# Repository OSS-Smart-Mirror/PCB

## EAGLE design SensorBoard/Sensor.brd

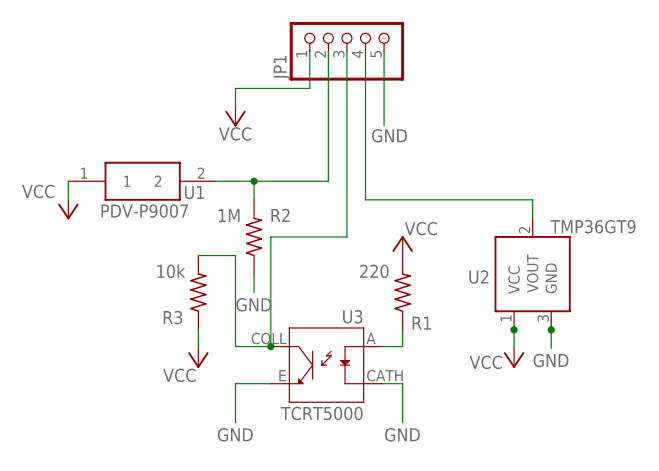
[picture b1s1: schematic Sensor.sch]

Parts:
JP1: PINHD-1X5; 1X05
R1: 220; R0805
R2: 1M; R0805
R3: 10k; R0805
U1: PDV-P9007
U2: TMP36GT9; TO-92
U3: TCRT5000; OPTO_TCRT5000

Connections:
GND: JP1.5, R2.1, U2.3 (GND), U3.CATH, U3.E
IR: JP1.3, R3.2, U3.COLL
LDR: JP1.2, R2.2, U1.2
unnamed: R1.1, U3.A
TEMP: JP1.4, U2.2 (VOUT)
VCC: JP1.1, R1.2, R3.1, U1.1, U2.1 (VCC)

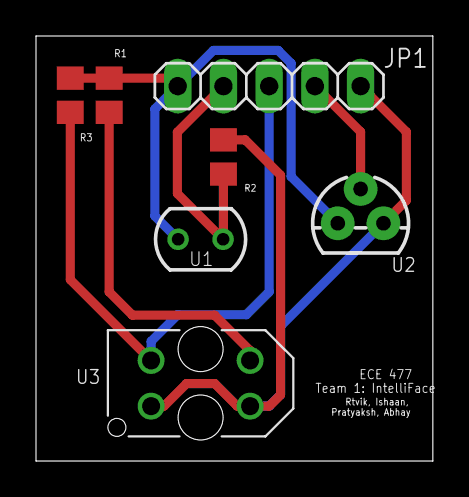
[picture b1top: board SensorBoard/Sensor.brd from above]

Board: 2 copper layers, 22.0 x 23.6 mm, 7 parts (0 on the bottom side), 6 nets.

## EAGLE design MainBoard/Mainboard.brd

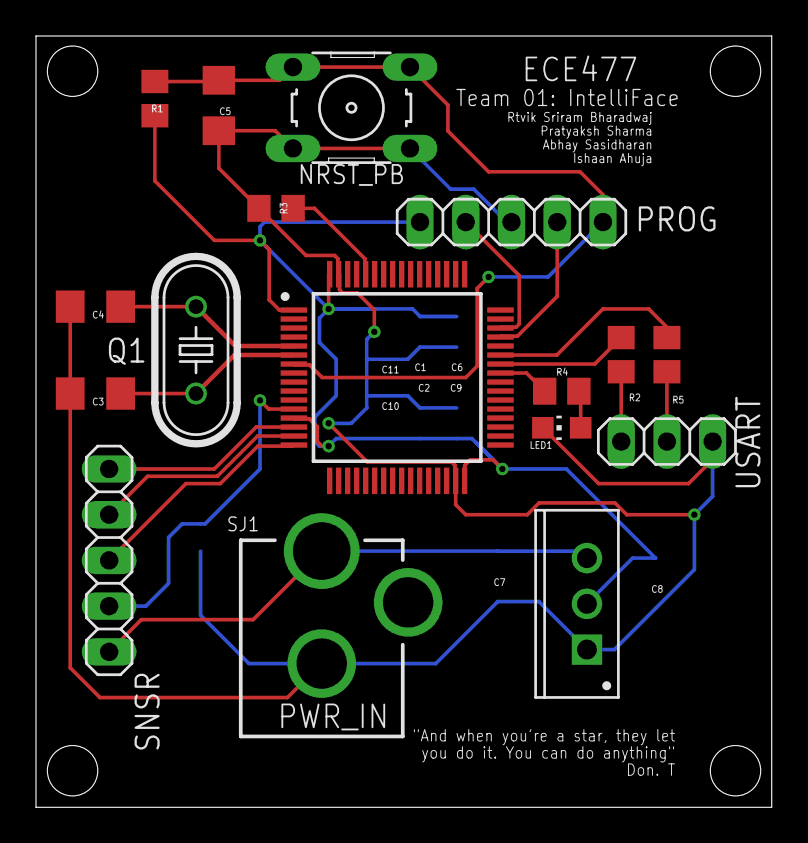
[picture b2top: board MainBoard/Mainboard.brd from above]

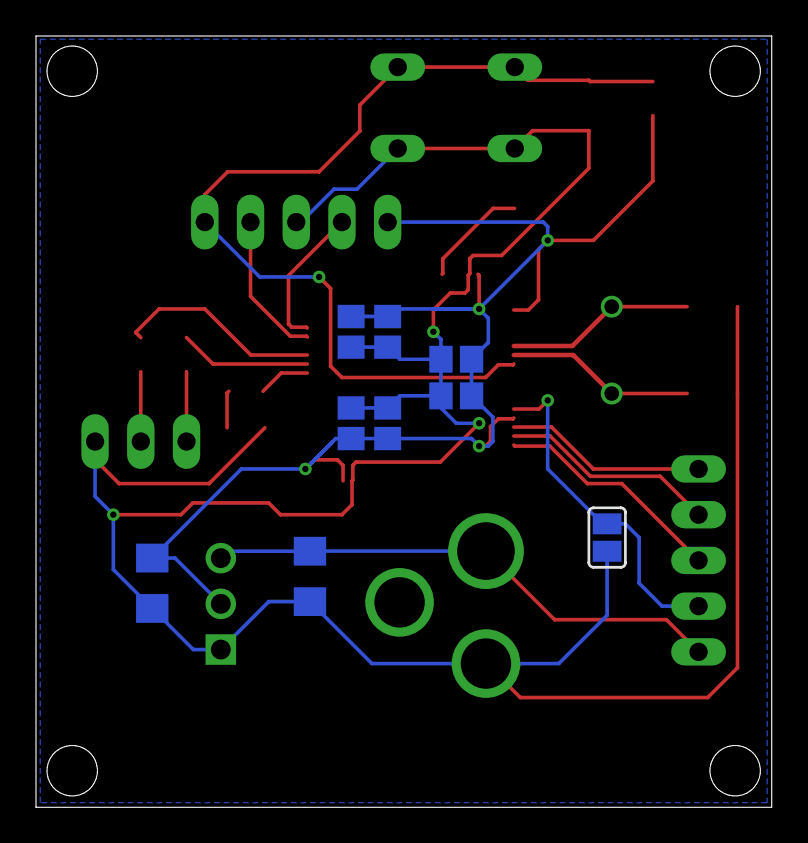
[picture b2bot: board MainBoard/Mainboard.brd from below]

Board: 2 copper layers, 40.9 x 42.8 mm, 26 parts (9 on the bottom side), 19 nets.

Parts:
5V-3V_REG: STMICROELECTRONICS_LD1117AV33STMICROELECTRONICS_L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; STMICROELECTRONICS_LD1117AV33_0
C1, C2, C9, C11: 100nF; C0805
C3, C4: 20pF; C1206
C5, C7: 100nF; C1206
C6, C10: 1uF; C0805
C8: 10uF; C1206
IC1: STM32F051R8T6; QFP50P1200X1200X160-64N
LED1: CHIP-LED0805
NRST_PB: B3F-10XX
PROG: 1X05
PWR_IN: 5V_IN; DCJACK_2MM_PTH
Q1: 8MHz; HC49U-V
R1: 100k; R0805
R2, R5: 100; R0805
R3: 510; R0805
R4: 330; R0805
SJ1: SJ
SNSR: 1X05
USART: 1X03

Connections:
5V: 5V-3V_REG.3, C7.1, PWR_IN.PWR, SNSR.1
AGND: IC1.12, SJ1.2, SNSR.2
BOOT0: IC1.60, R3.2
GND: 5V-3V_REG.1, C1.2, C2.2, C3.2, C4.2, C5.2, C6.2, C7.2, C8.2, C9.2, C10.1, C11.1, IC1.31, IC1.63, LED1.C, NRST_PB.1, NRST_PB.2, PROG.3, PWR_IN.GND, PWR_IN.GNDBREAK, R3.1, SJ1.1, USART.3
IR: IC1.15, SNSR.4
LDR: IC1.14, SNSR.5
unnamed: R2.1, USART.1
unnamed: R5.1, USART.2
unnamed: IC1.41, R4.2
unnamed: LED1.A, R4.1
unnamed: C3.1, IC1.6, Q1.2
unnamed: C4.1, IC1.5, Q1.1
NRST: C5.1, IC1.7, NRST_PB.3, NRST_PB.4, PROG.5, R1.1
SWCLK: IC1.45, PROG.4
SWDIO: IC1.46, PROG.2
TMP: IC1.16, SNSR.3
USART_RX: IC1.43, R5.2
USART_TX: IC1.42, R2.2
VDD: 5V-3V_REG.2, C1.1, C2.1, C6.1, C8.1, C9.1, C10.2, C11.2, IC1.1, IC1.13, IC1.32, IC1.64, PROG.1, R1.2

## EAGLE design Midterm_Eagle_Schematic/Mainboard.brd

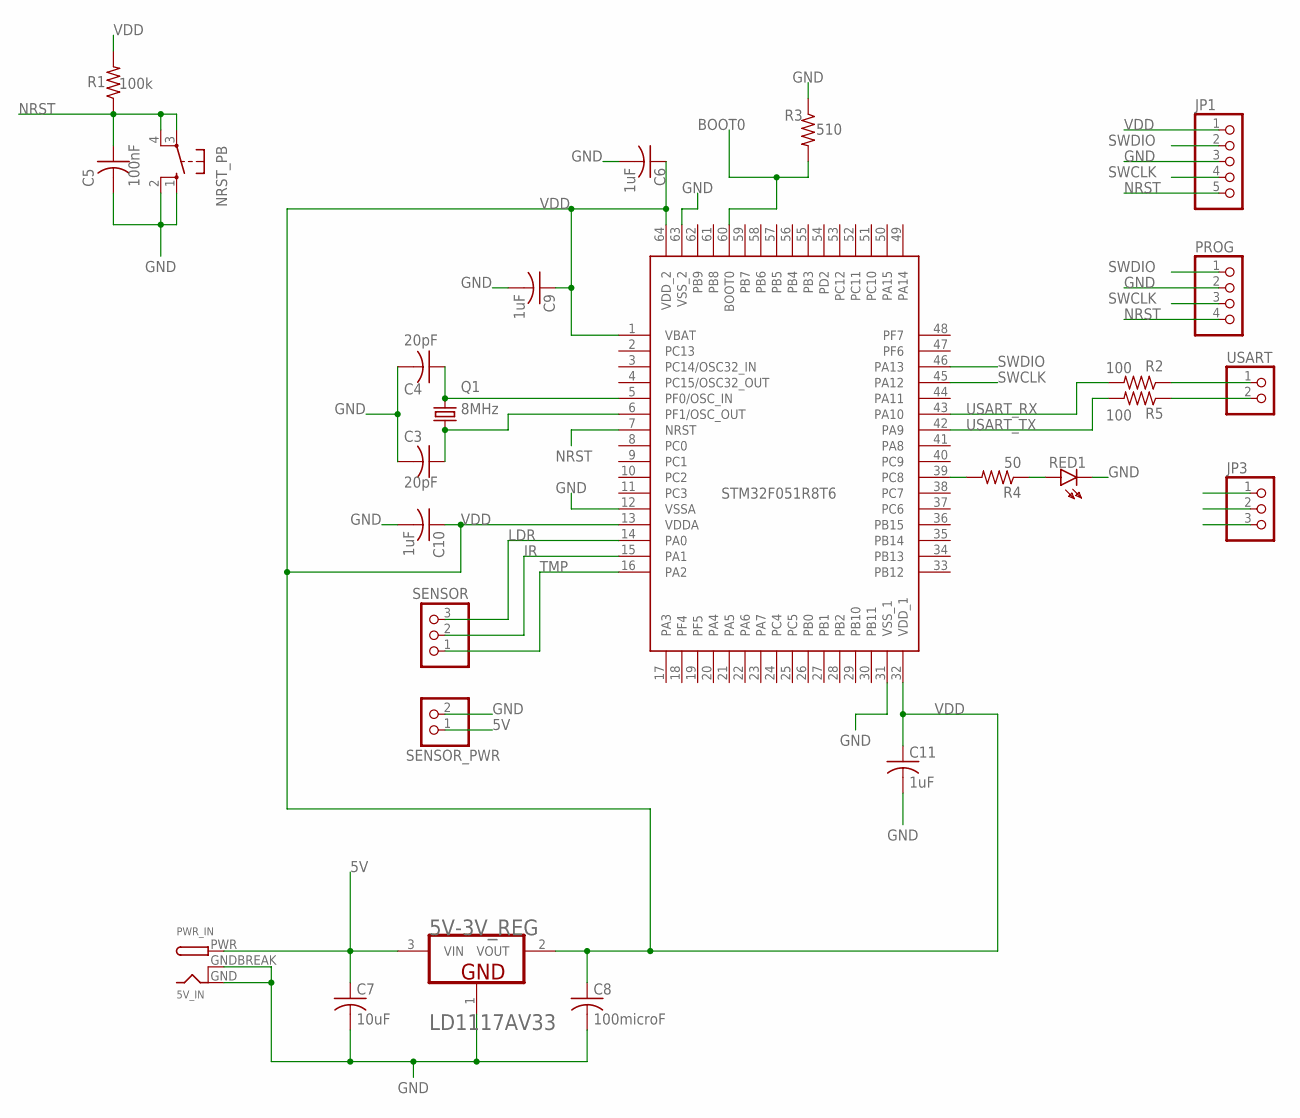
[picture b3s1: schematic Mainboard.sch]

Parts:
5V-3V_REG: STMICROELECTRONICS_LD1117AV33STMICROELECTRONICS_L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; STMICROELECTRONICS_LD1117AV33_0
C3, C4: 20pF; C1206
C5: 100nF; C1206
C6, C9, C10, C11: 1uF; C0805
C7: 10uF; C1206
C8: 100microF; C1206
IC1: STM32F051R8T6; QFP50P1200X1200X160-64N
JP1: PINHD-1X5; 1X05
JP2: SENSOR; 1X03
JP3: PINHD-1X3; 1X03
NRST_PB: 10-XX; B3F-10XX
PROG: PINHD-1X4; 1X04
PWR_IN: 5V_IN; DCJACK_2MM_PTH
Q1: 8MHz; HC49U-V
R1: 100k; 0204/5
R2, R5: 100; 0204/5
R3: 510; 0204/5
R4: 50; 0204/5
RED1: HLMP6
SENSOR_PWR: PINHD-1X2; 1X02
USART: PINHD-1X2; 1X02

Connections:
5V: 5V-3V_REG.3 (VIN), C7.1, PWR_IN.PWR, SENSOR_PWR.1
BOOT0: IC1.60 (BOOT0), R3.2
GND: 5V-3V_REG.1 (GND), C3.2, C4.2, C5.2, C6.2, C7.2, C8.2, C9.2, C10.2, C11.2, IC1.12 (VSSA), IC1.31 (VSS_1), IC1.63 (VSS_2), JP1.3, NRST_PB.1 (S), NRST_PB.2 (S1), PROG.2, PWR_IN.GND, PWR_IN.GNDBREAK, R3.1, RED1.K, SENSOR_PWR.2
IR: IC1.15 (PA1), JP2.2
LDR: IC1.14 (PA0), JP2.3
unnamed: IC1.39 (PC8), R4.2
unnamed: C3.1, IC1.6 (PF1/OSC_OUT), Q1.2
unnamed: R4.1, RED1.A
unnamed: C4.1, IC1.5 (PF0/OSC_IN), Q1.1
NRST: C5.1, IC1.7 (NRST), JP1.5, NRST_PB.3, NRST_PB.4 (P1), PROG.4, R1.1
SWCLK: IC1.45 (PA12), JP1.4, PROG.3
SWDIO: IC1.46 (PA13), JP1.2, PROG.1
TMP: IC1.16 (PA2), JP2.1
USART_RX: IC1.43 (PA10), R2.2
USART_RX1: R2.1, USART.1
USART_TX: IC1.42 (PA9), R5.2
USART_TX1: R5.1, USART.2
VDD: 5V-3V_REG.2 (VOUT), C6.1, C8.1, C9.1, C10.1, C11.1, IC1.1 (VBAT), IC1.13 (VDDA), IC1.32 (VDD_1), IC1.64 (VDD_2), JP1.1, R1.2

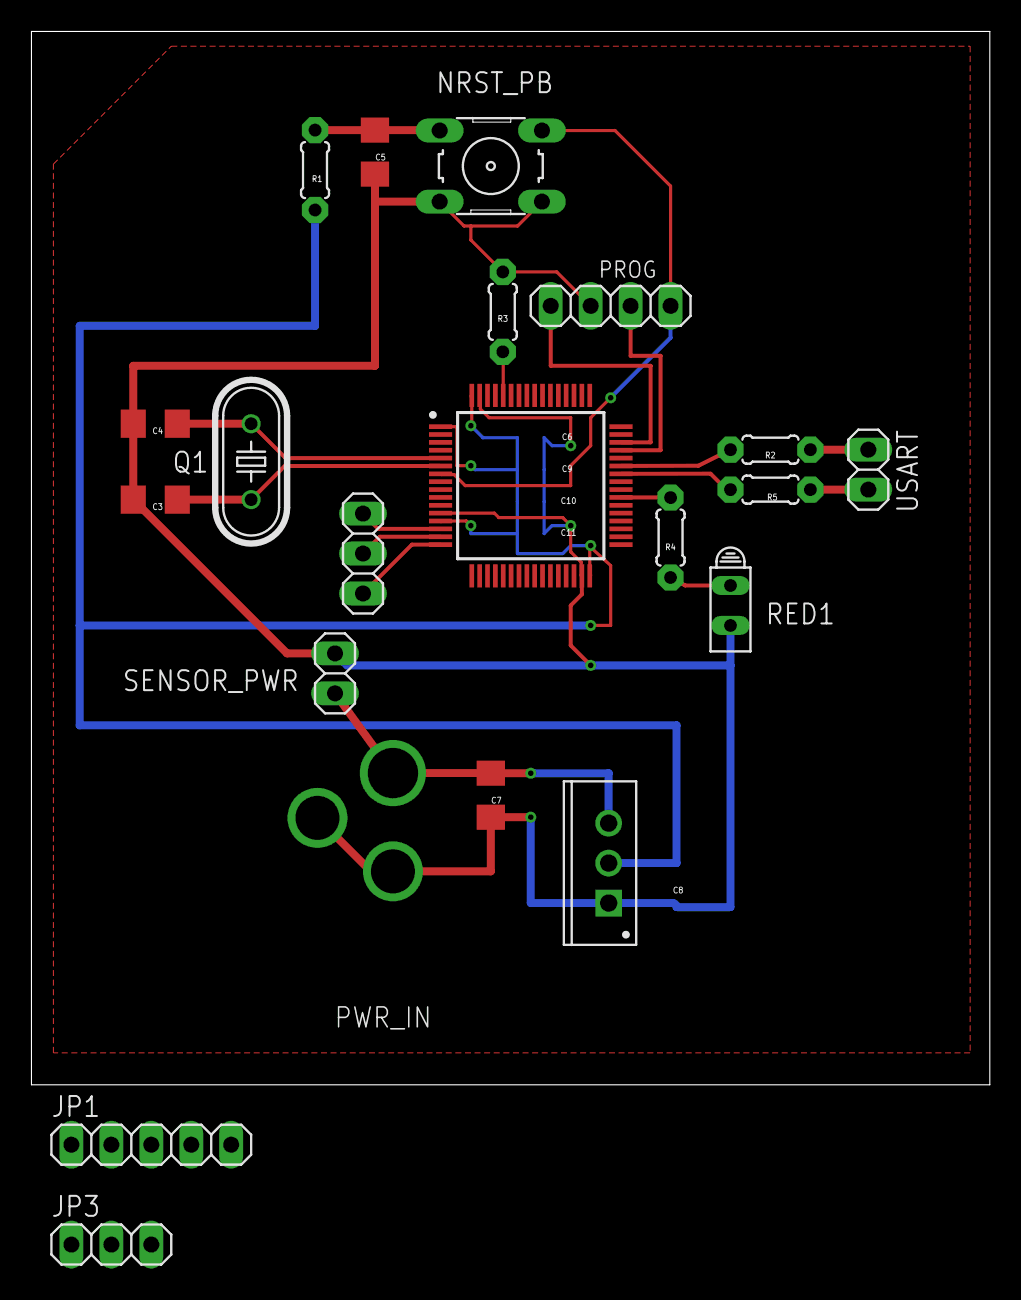
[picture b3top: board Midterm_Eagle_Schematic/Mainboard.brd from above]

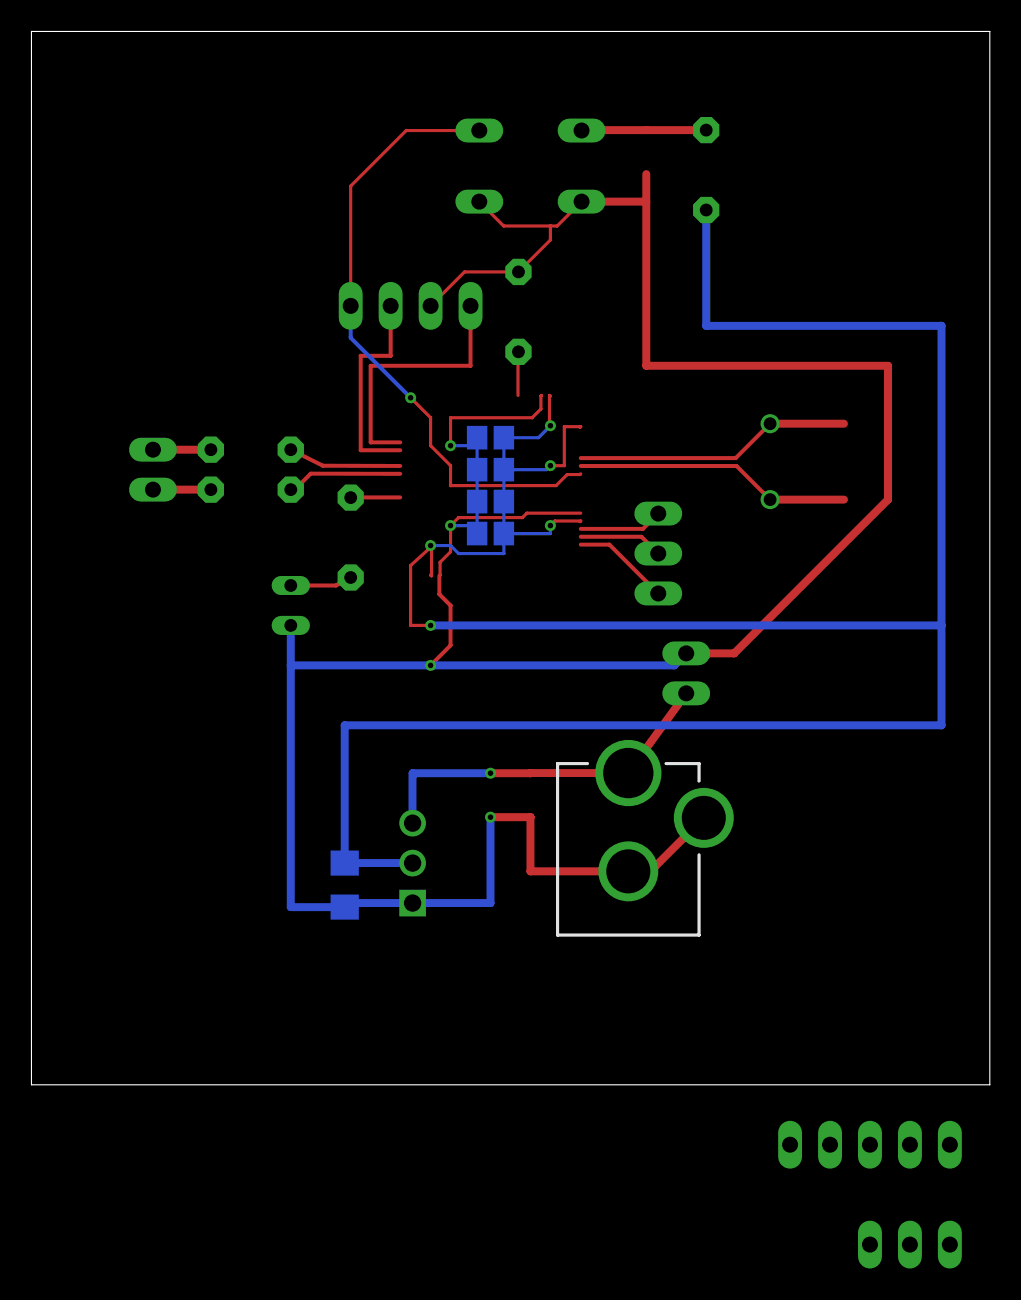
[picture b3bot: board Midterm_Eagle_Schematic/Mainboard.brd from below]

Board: 2 copper layers, 60.9 x 67.0 mm, 26 parts (6 on the bottom side), 18 nets.

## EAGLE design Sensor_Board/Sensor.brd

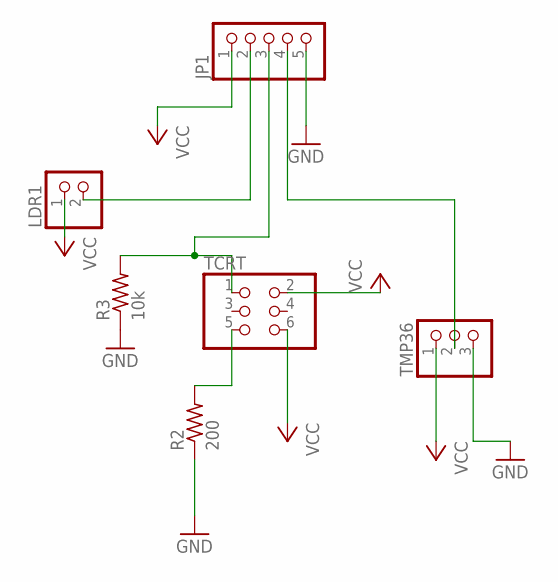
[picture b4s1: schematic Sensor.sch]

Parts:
JP1: PINHD-1X5; 1X05
LDR1: PINHD-1X2; 1X02
R2: 200; 0204/5
R3: 10k; 0204/5
TCRT: PINHD-2X3; 2X03
TMP36: PINHD-1X3; 1X03

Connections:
GND: JP1.5, R2.1, R3.1, TMP36.3
IR: JP1.3, R3.2, TCRT.1
LDR: JP1.2, LDR1.2
unnamed: R2.2, TCRT.5
TEMP: JP1.4, TMP36.2
VCC: JP1.1, LDR1.1, TCRT.2, TCRT.6, TMP36.1

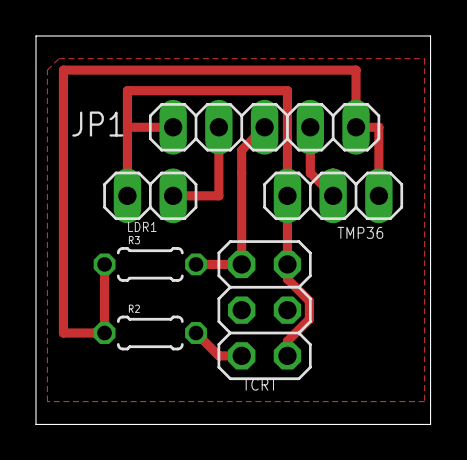
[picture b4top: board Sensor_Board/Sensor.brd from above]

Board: 2 copper layers, 21.9 x 21.6 mm, 6 parts (0 on the bottom side), 6 nets.

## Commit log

2019-10-07 Adding draft 1 pcb files
2019-10-07 adding lib files
2019-10-09 Adding midterm review schema
2019-10-10 updated board schematic
2019-10-10 adding more libs
2019-10-11 adding new main and sensor boards
2019-10-11 adding annots
2019-10-14 adding name and comments
